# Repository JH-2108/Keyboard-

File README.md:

# Custom 87 key Mechanical Keybord
This is a custom-designed 80% mechanical keyboard built around the Raspberry Pi Pico RP2040 microcontroller. The project combines a custom PCB, individually soldered mechanical switches, an OLED display, and a rotary encoder into a compact keyboard designed for everyday typing and customization. 

# Features 
- **87 key layout**: A compact layout that retains the function row, arrow keys, and navigation clusters.
- **Custom PCB**: A purpose-designed printed circuit board for the keyboard matrix and peripherals.
- **Direct-solder switches**: MX-compatible mechanical switches soldered directly to the PCB, without hot-swap pockets.
- **RP2040 controller**: A raspberry Pi Pico handles keyboard input and peripheral communication.
- **OLED Display**: A small I2C display for keyboard status and custom information.
- **Rotary encoder**: Provides rotary input and a push-button control.
- **Custom enclosure**: A case and plate designed to support and protect the assembly.

# Hardware architecture 
The Raspberry Pi Pico RP2040 scans a keyboard switch matrix. Each key uses a mechanical switch and a 1N418 diode to help prevent unintended electrical interactions when multiple keys are pressed. 

The OLED communications with a controller over I2C. The rotary encoder provides rotational input and a push-button signal. Firmware interprets these inputs and translates key presses into keyboard reports sent to the host computer over USB. 

# Firmware
The firmware will run on the Raspberry Pi Pico RP2040 and provide: 
- Keyboard matrix scanning.
- USB keyboard input reporting.
- OLED communication over I2C.
- Rotary encoder and push-button handling.

The firmware framework and keymap will be documented here once finalized. 

# Assembly
1. Inspect the fabricated PCB for manufacturing defects.
2. Solder the diodes in the correct orientation.
3. Solder the mechanical switches directly to the PCB.
4. Install the Raspberry Pi Pico and peripheral connections according to the finalized design.
5. Connect the OLED and rotary encoder.
6. Fit the stabilizers, keycaps, plate, and case.
7. Flash the firmware and test every key and peripheral.
8. Verify USB connectivity and check for unintended key presses.

# Project pictures
**PCB design** 

A photo will be added here 

**Schematic** 

A photo will be added here 

**3D case**

A photo will be added here 

**Complete physical build** 

A photo will be added here

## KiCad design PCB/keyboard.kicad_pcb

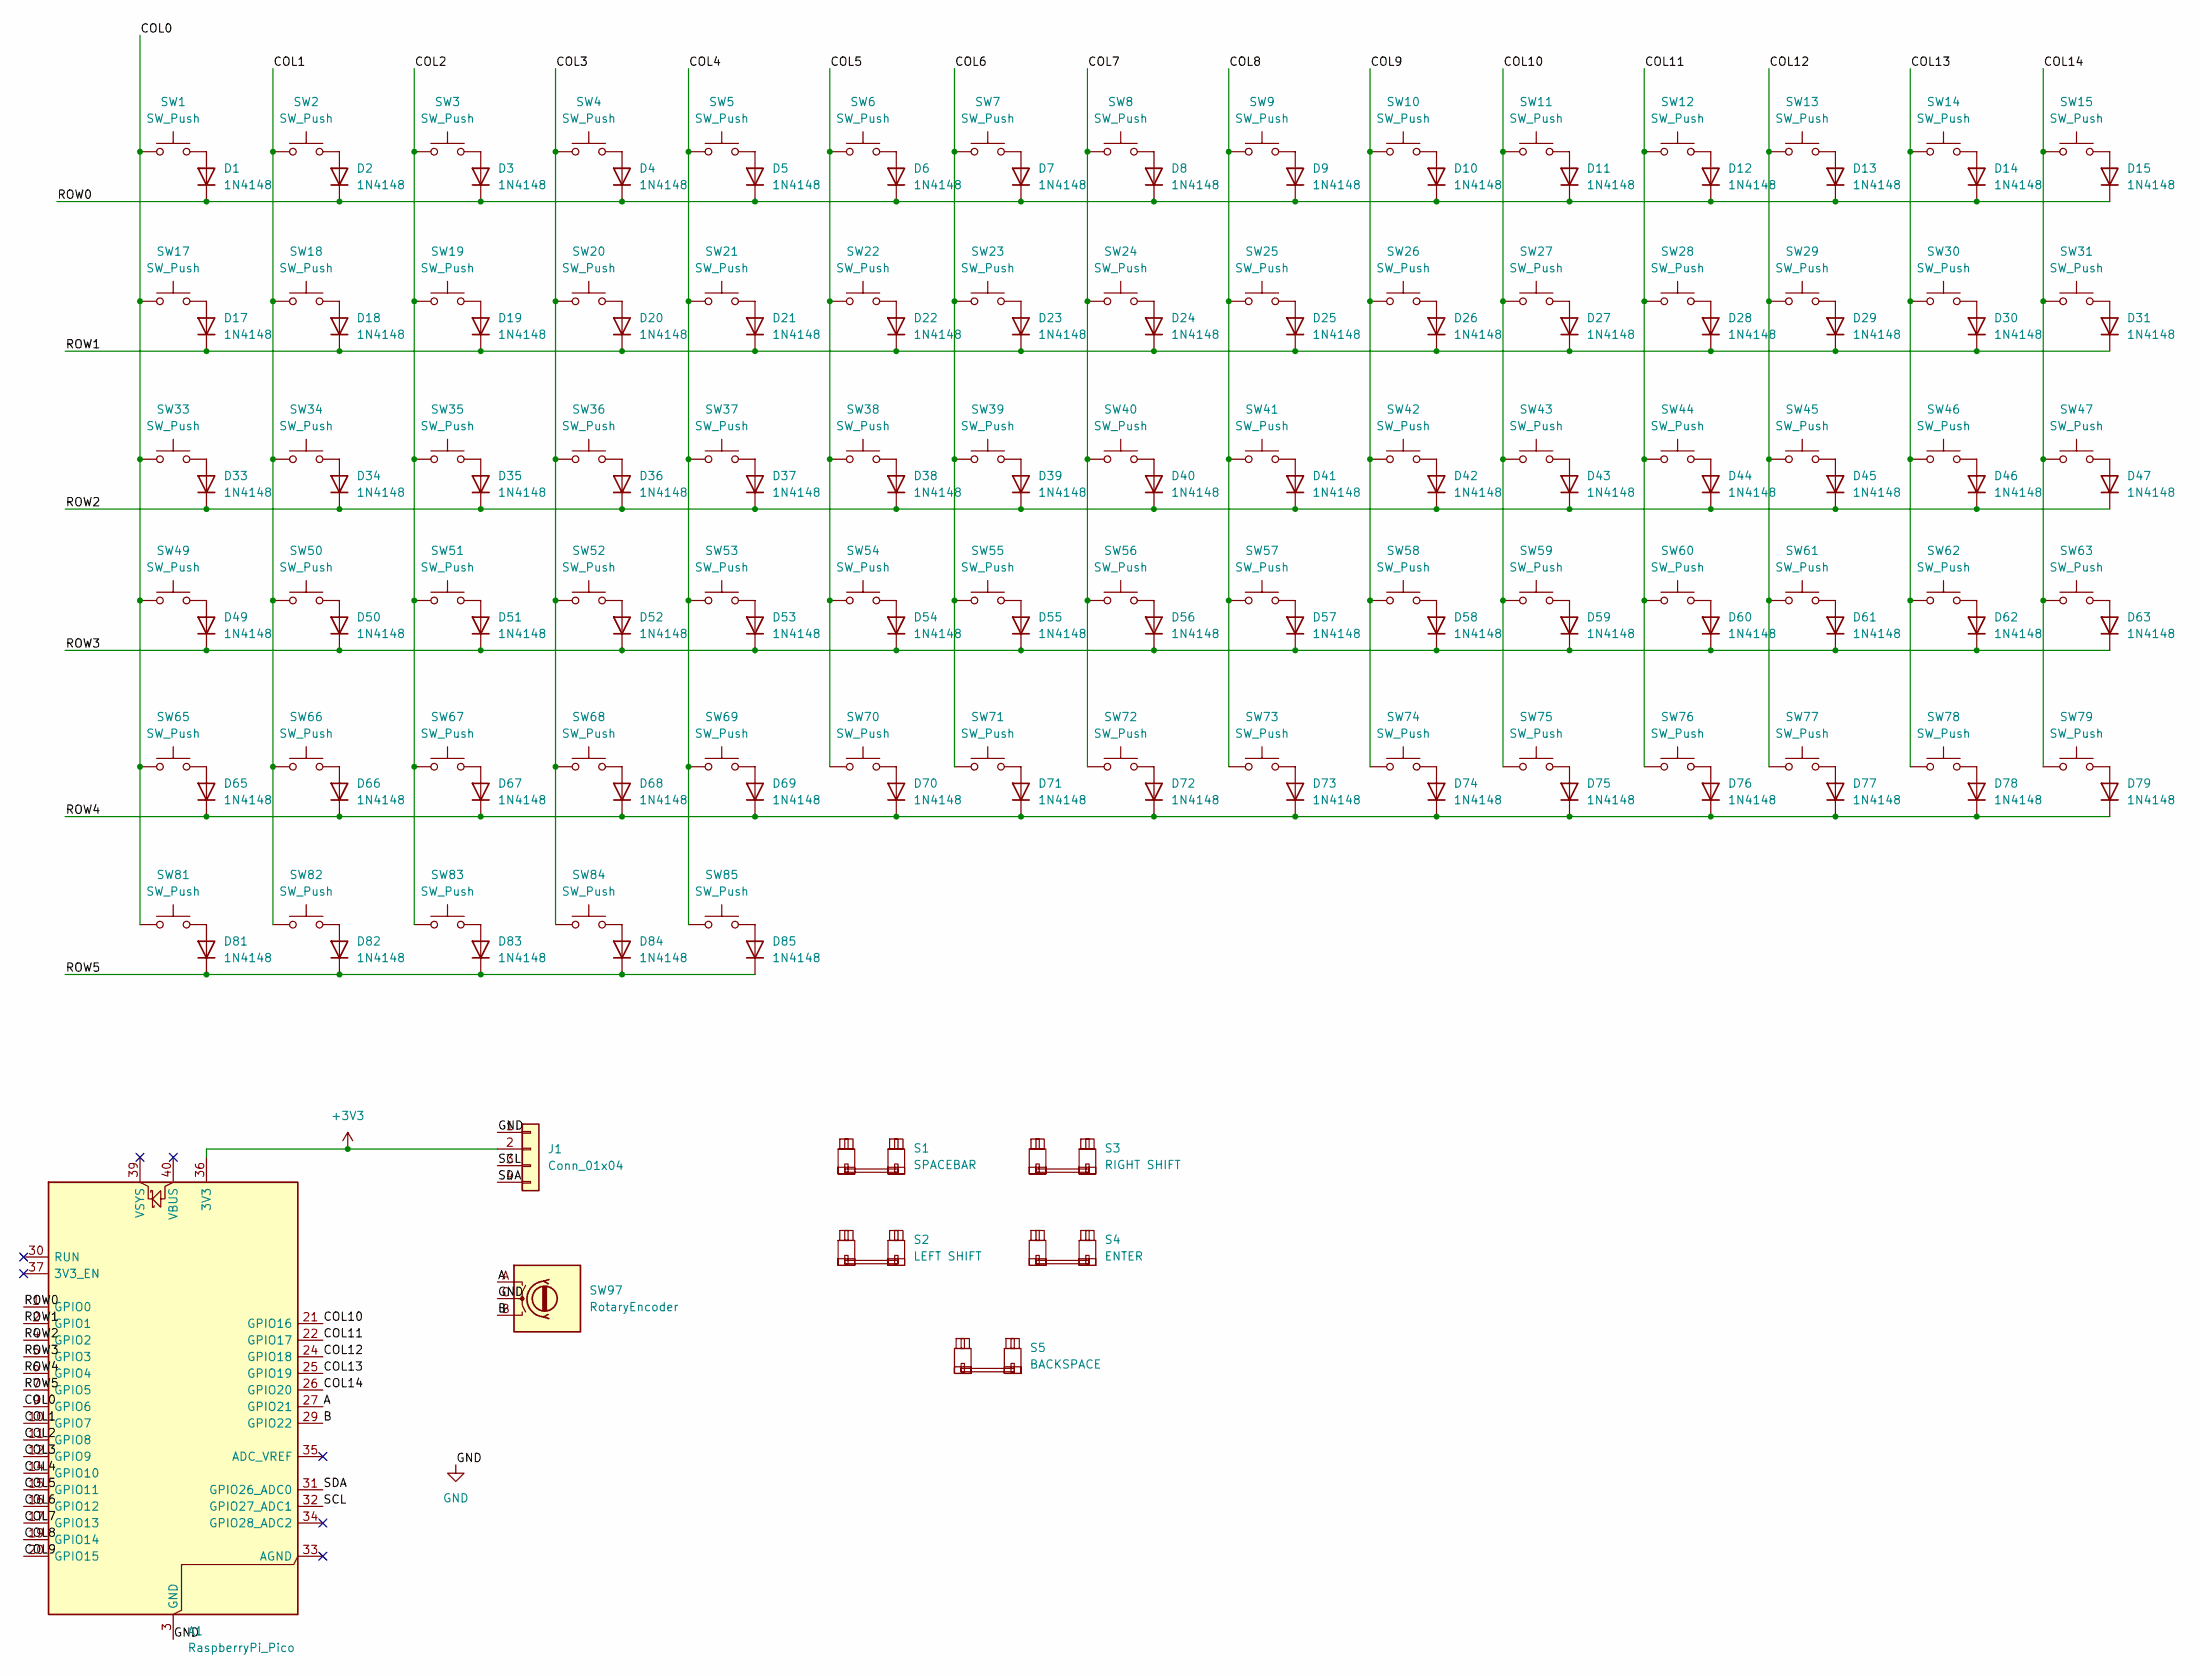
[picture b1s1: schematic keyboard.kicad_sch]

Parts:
A1: RaspberryPi_Pico; RaspberryPi_Pico_Common_THT
D1, D2, D3, D4, D5, D6, D7, D8, D9, D10, D11, D12, D13, D14, D15, D17, D18, D19, D20, D21, D22, D23, D24, D25, D26, D27, D28, D29, D30, D31, D33, D34, D35, D36, D37, D38, D39, D40, D41, D42, D43, D44, D45, D46, D47, D49, D50, D51, D52, D53, D54, D55, D56, D57, D58, D59, D60, D61, D62, D63, D65, D66, D67, D68, D69, D70, D71, D72, D73, D74, D75, D76, D77, D78, D79, D81, D82, D83, D84, D85: 1N4148; D_DO-35_SOD27_P7.62mm_Horizontal
J1: Conn_01x04; ER_OLEDM0.91_1x-I2C
S1: SPACEBAR; STAB_MX_P_6.25u
S2: LEFT SHIFT; STAB_MX_2.25u
S3: RIGHT SHIFT; STAB_MX_2.75u
S4: ENTER; STAB_MX_2.25u
S5: BACKSPACE; STAB_MX_2u
SW1, SW2, SW3, SW4, SW5, SW6, SW7, SW8, SW9, SW10, SW11, SW12, SW13, SW14, SW15, SW17, SW18, SW19, SW20, SW21, SW22, SW23, SW24, SW25, SW26, SW27, SW28, SW29, SW31, SW33, SW34, SW35, SW36, SW37, SW38, SW39, SW40, SW41, SW42, SW43, SW46, SW47, SW49, SW50, SW51, SW52, SW53, SW54, SW55, SW56, SW57, SW58, SW59, SW60, SW61, SW62, SW63, SW65, SW66, SW67, SW68, SW69, SW70, SW71, SW75, SW81, SW82, SW83, SW84, SW85: SW_Push; SW_Cherry_MX_1.00u_PCB
SW30, SW44: SW_Push; SW_Cherry_MX_1.50u_PCB
SW45: SW_Push; SW_Cherry_MX_1.75u_PCB
SW72, SW73, SW74, SW76, SW77, SW78, SW79: SW_Push; SW_Cherry_MX_1.25u_PCB
SW97: RotaryEncoder; RotaryEncoder_Alps_EC11E-Switch_Vertical_H20mm

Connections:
+3V3: A1.36 (3V3), J1.2
/A: A1.27 (GPIO21), SW97.A
/B: A1.29 (GPIO22), SW97.B
/COL0: A1.9 (GPIO6), SW1.1, SW17.1, SW33.1, SW49.1, SW65.1, SW81.1
/COL1: A1.10 (GPIO7), SW2.1, SW18.1, SW34.1, SW50.1, SW66.1, SW82.1
/COL2: A1.11 (GPIO8), SW3.1, SW19.1, SW35.1, SW51.1, SW67.1, SW83.1
/COL3: A1.12 (GPIO9), SW4.1, SW20.1, SW36.1, SW52.1, SW68.1, SW84.1
/COL4: A1.14 (GPIO10), SW5.1, SW21.1, SW37.1, SW53.1, SW69.1, SW85.1
/COL5: A1.15 (GPIO11), SW6.1, SW22.1, SW38.1, SW54.1, SW70.1
/COL6: A1.16 (GPIO12), SW7.1, SW23.1, SW39.1, SW55.1, SW71.1
/COL7: A1.17 (GPIO13), SW8.1, SW24.1, SW40.1, SW56.1, SW72.1
/COL8: A1.19 (GPIO14), SW9.1, SW25.1, SW41.1, SW57.1, SW73.1
/COL9: A1.20 (GPIO15), SW10.1, SW26.1, SW42.1, SW58.1, SW74.1
/COL10: A1.21 (GPIO16), SW11.1, SW27.1, SW43.1, SW59.1, SW75.1
/COL11: A1.22 (GPIO17), SW12.1, SW28.1, SW44.1, SW60.1, SW76.1
/COL12: A1.24 (GPIO18), SW13.1, SW29.1, SW45.1, SW61.1, SW77.1
/COL13: A1.25 (GPIO19), SW14.1, SW30.1, SW46.1, SW62.1, SW78.1
/COL14: A1.26 (GPIO20), SW15.1, SW31.1, SW47.1, SW63.1, SW79.1
/ROW0: A1.1 (GPIO0), D1.1 (K), D2.1 (K), D3.1 (K), D4.1 (K), D5.1 (K), D6.1 (K), D7.1 (K), D8.1 (K), D9.1 (K), D10.1 (K), D11.1 (K), D12.1 (K), D13.1 (K), D14.1 (K), D15.1 (K)
/ROW1: A1.2 (GPIO1), D17.1 (K), D18.1 (K), D19.1 (K), D20.1 (K), D21.1 (K), D22.1 (K), D23.1 (K), D24.1 (K), D25.1 (K), D26.1 (K), D27.1 (K), D28.1 (K), D29.1 (K), D30.1 (K), D31.1 (K)
/ROW2: A1.4 (GPIO2), D33.1 (K), D34.1 (K), D35.1 (K), D36.1 (K), D37.1 (K), D38.1 (K), D39.1 (K), D40.1 (K), D41.1 (K), D42.1 (K), D43.1 (K), D44.1 (K), D45.1 (K), D46.1 (K), D47.1 (K)
/ROW3: A1.5 (GPIO3), D49.1 (K), D50.1 (K), D51.1 (K), D52.1 (K), D53.1 (K), D54.1 (K), D55.1 (K), D56.1 (K), D57.1 (K), D58.1 (K), D59.1 (K), D60.1 (K), D61.1 (K), D62.1 (K), D63.1 (K)
/ROW4: A1.6 (GPIO4), D65.1 (K), D66.1 (K), D67.1 (K), D68.1 (K), D69.1 (K), D70.1 (K), D71.1 (K), D72.1 (K), D73.1 (K), D74.1 (K), D75.1 (K), D76.1 (K), D77.1 (K), D78.1 (K), D79.1 (K)
/ROW5: A1.7 (GPIO5), D81.1 (K), D82.1 (K), D83.1 (K), D84.1 (K), D85.1 (K)
/SCL: A1.32 (GPIO27_ADC1), J1.3
/SDA: A1.31 (GPIO26_ADC0), J1.4
GND: A1.3 (GND), A1.8 (GND), A1.13 (GND), A1.18 (GND), A1.23 (GND), A1.28 (GND), A1.38 (GND), J1.1, SW97.C
unnamed: D1.2 (A), SW1.2
unnamed: D2.2 (A), SW2.2
unnamed: D3.2 (A), SW3.2
unnamed: D4.2 (A), SW4.2
unnamed: D5.2 (A), SW5.2
unnamed: D6.2 (A), SW6.2
unnamed: D7.2 (A), SW7.2
unnamed: D8.2 (A), SW8.2
unnamed: D9.2 (A), SW9.2
unnamed: D10.2 (A), SW10.2
unnamed: D11.2 (A), SW11.2
unnamed: D12.2 (A), SW12.2
unnamed: D13.2 (A), SW13.2
unnamed: D14.2 (A), SW14.2
unnamed: D15.2 (A), SW15.2
unnamed: D17.2 (A), SW17.2
unnamed: D18.2 (A), SW18.2
unnamed: D19.2 (A), SW19.2
unnamed: D20.2 (A), SW20.2
unnamed: D21.2 (A), SW21.2
unnamed: D22.2 (A), SW22.2
unnamed: D23.2 (A), SW23.2
unnamed: D24.2 (A), SW24.2
unnamed: D25.2 (A), SW25.2
unnamed: D26.2 (A), SW26.2
unnamed: D27.2 (A), SW27.2
unnamed: D28.2 (A), SW28.2
unnamed: D29.2 (A), SW29.2
unnamed: D30.2 (A), SW30.2
unnamed: D31.2 (A), SW31.2
unnamed: D33.2 (A), SW33.2
unnamed: D34.2 (A), SW34.2
unnamed: D35.2 (A), SW35.2
unnamed: D36.2 (A), SW36.2
unnamed: D37.2 (A), SW37.2
unnamed: D38.2 (A), SW38.2
unnamed: D39.2 (A), SW39.2
unnamed: D40.2 (A), SW40.2
unnamed: D41.2 (A), SW41.2
unnamed: D42.2 (A), SW42.2
unnamed: D43.2 (A), SW43.2
unnamed: D44.2 (A), SW44.2
unnamed: D45.2 (A), SW45.2
unnamed: D46.2 (A), SW46.2
unnamed: D47.2 (A), SW47.2
unnamed: D49.2 (A), SW49.2
unnamed: D50.2 (A), SW50.2
unnamed: D51.2 (A), SW51.2
unnamed: D52.2 (A), SW52.2
unnamed: D53.2 (A), SW53.2
unnamed: D54.2 (A), SW54.2
unnamed: D55.2 (A), SW55.2
unnamed: D56.2 (A), SW56.2
unnamed: D57.2 (A), SW57.2
unnamed: D58.2 (A), SW58.2
unnamed: D59.2 (A), SW59.2
unnamed: D60.2 (A), SW60.2
unnamed: D61.2 (A), SW61.2
unnamed: D62.2 (A), SW62.2
unnamed: D63.2 (A), SW63.2
unnamed: D65.2 (A), SW65.2
unnamed: D66.2 (A), SW66.2
unnamed: D67.2 (A), SW67.2
unnamed: D68.2 (A), SW68.2
unnamed: D69.2 (A), SW69.2
unnamed: D70.2 (A), SW70.2
unnamed: D71.2 (A), SW71.2
unnamed: D72.2 (A), SW72.2
unnamed: D73.2 (A), SW73.2
unnamed: D74.2 (A), SW74.2
unnamed: D75.2 (A), SW75.2
unnamed: D76.2 (A), SW76.2
unnamed: D77.2 (A), SW77.2
unnamed: D78.2 (A), SW78.2
unnamed: D79.2 (A), SW79.2
unnamed: D81.2 (A), SW81.2
unnamed: D82.2 (A), SW82.2
unnamed: D83.2 (A), SW83.2
unnamed: D84.2 (A), SW84.2
unnamed: D85.2 (A), SW85.2

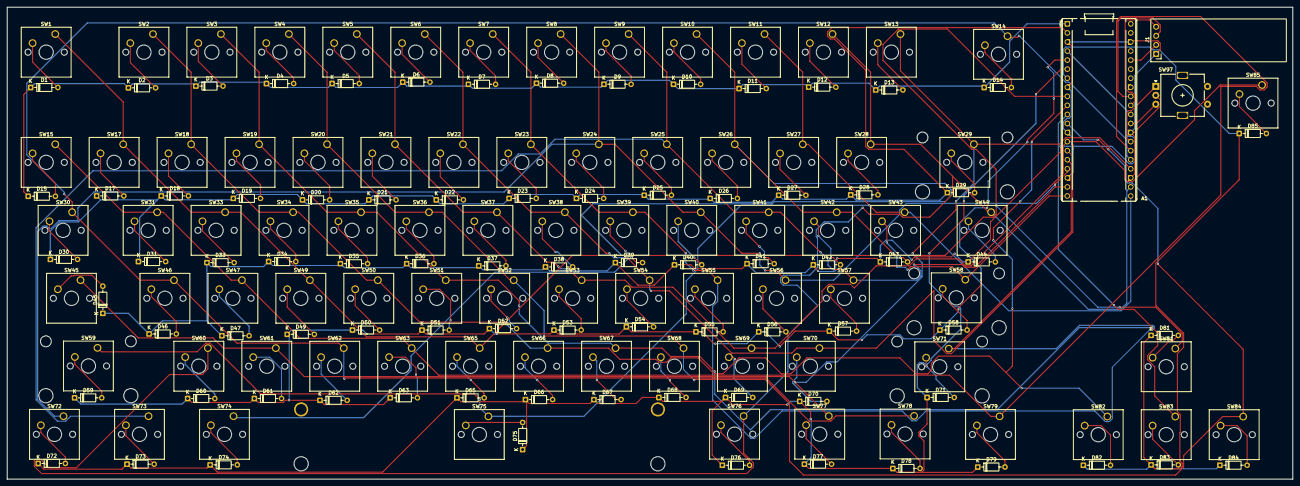
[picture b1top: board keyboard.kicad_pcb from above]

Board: 2 copper layers, 360.4 x 132.3 mm, 168 parts (0 on the bottom side), 107 nets.
